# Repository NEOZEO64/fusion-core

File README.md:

# FUSION CORE (synthesizer)

## Aims

- No aim lol
- Get to know delicious circuits (experimenting a lot)
- Use them in crude ways to generate sounds
- Learn how to design circuits & professionally manufacture them with KiCad
- Learn whats possible with analog circuits and what's not
- Have a lot of fun without the need of programming

- Get an overview of electronic parts out there
- Manage a big project
- Make ambient dub techno at the end lol

## Resources
- Books
    - Make: Analog Synthesizers (from Music from outer space)
    - The Art of Electronics
    - Make: Electronics & Make: More Electronics
    - Encyclopedia of Electronic Components (Vol. 1, Vol. 2, Vol. 3)
    - Engineers Mini-Notebooks
- Internet
    - https://www.lookmumnocomputer.com/
    - https://www.eddybergman.com/
    - https://www.birthofasynth.com/Thomas_Henry/TH_main.html
    - https://musicfromouterspace.com/
    - https://www.schmitzbits.de/index.html
    - https://www.ericasynths.lv/
    - and a lot more!
- University for background theory
    - Electronics I & II
    - Signals & Systems, Control Systems
    - Communications Engineering
    - Computer Engineering

## Gallery

DIY dual 12V power supply + 5V (combined switched mode & linear regulated)

My first module! Still very early, but reliable 1V/oct frequency control and all outputs (Triangle, Saw, Rectangle) have the same voltage levels

Obviously go to Look Mum no Computer concert!

Test circuits with chaotic wiring

Borrow devices from student research center

## Module Specifications
- ±12V, 5V Power Supply
- 16cm high, n * 2cm wide (Eurorack is too small, Cosmo too large)

- PCB-Color: Green
- Different front-plate materials (wooden, metal, PVC)

# Level 1: Basic Synth

## Chapter 1: Case
- It should be a wooden box sprayed black with fancy neon art or something

## Chapter 2: PSU
- found a better one than my own diy thing (RT65-B)

## Chapter 3: 3x VCO 
- still experimenting and learning how to design modules with input / output protection
- but first VCO tests work based on AS3340/CEM3340

Knobs:
- Big Frequency Knob
- Fine Frequency Knob
- PWM Knob

Inputs:
- PWM
- 1V/Oct
- Hard Sync
- Soft Sync

Outputs:
- Triangle
- Sawtooth
- Rectangle

## Chapter 4: 2x VCF
- First design workes based on LM13700 Operational Transconductance Amplifier, but I want to make sure it workes in every situation and the output is in voltage bounds

Knobs:
- Cutoff
- Resonance
- Drive

Inputs:
- Cutoff
- Resonance
- Drive

Output:
- Low Pass
- Band pass
- High Pass

## Chapter 5: 4x VCA

VU Meter?

Knobs:
- Volume

Inputs:
- Audio in
- CV in

Outputs:
- Audio out

## Chapter 6: 2x 4-channel Mixer
Knobs:
- Channel 1 Volume
- Channel 2 Volume
- Channel 3 Volume
- Channel 4 Volume

Inputs:
- Audio Channel 1
- Audio Channel 2
- Audio Channel 3
- Audio Channel 4

Output
- Audio Sum

## Chapter 7: Teensy 4.1 as digital signal processor for reverb / echo / distortion effects

Knobs:
- Mode
- Mod 1 (Reverb Room Size    / Echo Clock Speed)
- Mod 2 (Reverb Decay Length / Echo Feedback)

Input:
- Left Audio In
- Optional Right Audio In
- Mod 1 (Reverb Room Size    / Echo Clock Speed)

Output:
- Left Audio Out
- Right Audio Out

## Chapter 8: Audio Out (Headphones, Line Out)
- Input buffering Input / Output durch OpAmp?

- Dual Mono to Stereo
- Headphone Out
- Volume Knob
- Vu Meter

# Level 3: LMNC AAAPPPCCC Module

# Level 4: Triangle to Sine Wave Conversion

# Level 5: Beat Extension

## Chapter 1: Splitter

## Chapter 2: Clock

## Chapter 3: Clock Divider

## Chapter 4: Counter

## Chapter 5: ADSR

## Chapter 6: Manual Trigger / Gate

## Chapter 7: Sample & Hold

## Chapter 8: LFO

## Chapter 9: Constant voltage source

## Chapter 10: Signal voltage offset

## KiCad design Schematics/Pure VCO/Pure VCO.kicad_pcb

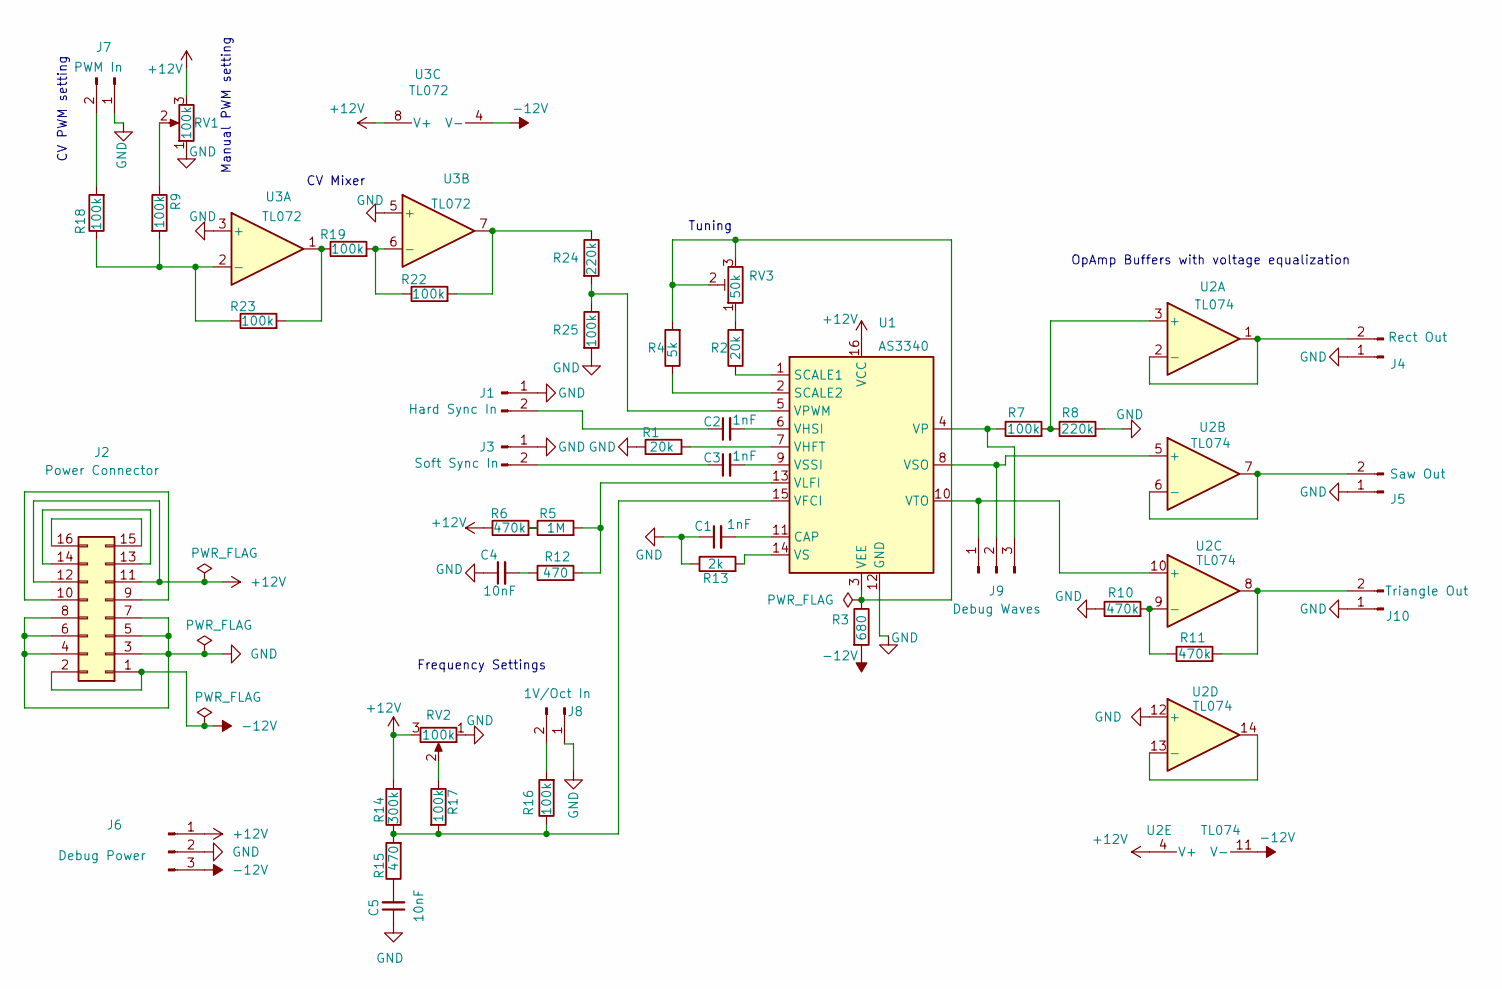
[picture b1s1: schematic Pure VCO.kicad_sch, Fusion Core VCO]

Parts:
C1: 1nF; C_Disc_D14.5mm_W5.0mm_P10.00mm
C2, C3: 1nF; C_Disc_D4.3mm_W1.9mm_P5.00mm
C4, C5: 10nF; C_Disc_D4.3mm_W1.9mm_P5.00mm
J1: Hard Sync In; PinHeader_1x02_P2.54mm_Vertical
J2: Power Connector; IDC-Header_2x08_P2.54mm_Vertical
J3: Soft Sync In; PinHeader_1x02_P2.54mm_Vertical
J4: Rect Out; PinHeader_1x02_P2.54mm_Vertical
J5: Saw Out; PinHeader_1x02_P2.54mm_Vertical
J6: Debug Power; PinHeader_1x03_P2.54mm_Vertical
J7: PWM In; PinHeader_1x02_P2.54mm_Vertical
J8: 1V/Oct In; PinHeader_1x02_P2.54mm_Vertical
J9: Debug Waves; PinHeader_1x03_P2.54mm_Vertical
J10: Triangle Out; PinHeader_1x02_P2.54mm_Vertical
R1, R2: 20k; R_Axial_DIN0207_L6.3mm_D2.5mm_P7.62mm_Horizontal
R3: 680; R_Axial_DIN0207_L6.3mm_D2.5mm_P7.62mm_Horizontal
R4: 5k; R_Axial_DIN0207_L6.3mm_D2.5mm_P7.62mm_Horizontal
R5: 1M; R_Axial_DIN0207_L6.3mm_D2.5mm_P7.62mm_Horizontal
R6, R10, R11: 470k; R_Axial_DIN0207_L6.3mm_D2.5mm_P7.62mm_Horizontal
R7, R9, R16, R17, R18, R19, R22, R23, R25: 100k; R_Axial_DIN0207_L6.3mm_D2.5mm_P7.62mm_Horizontal
R8, R24: 220k; R_Axial_DIN0207_L6.3mm_D2.5mm_P7.62mm_Horizontal
R12, R15: 470; R_Axial_DIN0207_L6.3mm_D2.5mm_P7.62mm_Horizontal
R13: 2k; R_Axial_DIN0207_L6.3mm_D2.5mm_P7.62mm_Horizontal
R14: 300k; R_Axial_DIN0207_L6.3mm_D2.5mm_P7.62mm_Horizontal
RV1, RV2: 100k; Potentiometer_Bourns_3386C_Horizontal
RV3: 50k; Potentiometer_Bourns_3266Y_Vertical
U1: AS3340; DIP-16_W7.62mm_Socket
U2: TL074; DIP-14_W7.62mm_Socket
U3: TL072; DIP-8_W7.62mm_Socket

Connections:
+12V: J2.11, J2.12, J6.1, R6.1, R14.2, RV1.3, RV2.3, U1.16 (VCC), U2.4 (V+), U3.8 (V+)
-12V: J2.1, J2.2, J6.3, R3.2, U2.11 (V-), U3.4 (V-)
GND: C1.1, C4.1, C5.1, J1.1, J2.3, J2.4, J2.5, J2.6, J2.7, J2.8, J3.1, J4.1, J5.1, J6.2, J7.1, J8.1, J10.1, R1.1, R8.2, R10.1, R13.1, R25.2, RV1.1, RV2.1, U1.12 (GND), U2.12 (+), U3.3 (+), U3.5 (+)
unnamed: C4.2, R12.1
unnamed: C5.2, R15.1
unnamed: C2.1, J1.2
unnamed: J2.9, J2.10
unnamed: J2.13, J2.14
unnamed: J2.15, J2.16
unnamed: C3.1, J3.2
unnamed: J4.2, U2.1, U2.2 (-)
unnamed: J5.2, U2.6 (-), U2.7
unnamed: J7.2, R18.2
unnamed: J8.2, R16.2
unnamed: J9.1, U1.10 (VTO), U2.10 (+)
unnamed: J9.2, U1.8 (VSO), U2.5 (+)
unnamed: J9.3, R7.1, U1.4 (VP)
unnamed: J10.2, R11.2, U2.8
unnamed: R2.2, RV3.1
unnamed: R5.1, R6.2
unnamed: R9.1, RV1.2
unnamed: R17.1, RV2.2
unnamed: R19.1, R23.2, U3.1
unnamed: R22.2, R24.1, U3.7
unnamed: C1.2, U1.11 (CAP)
unnamed: R2.1, U1.1 (SCALE1)
unnamed: R4.1, U1.2 (SCALE2)
unnamed: R3.1, R4.2, RV3.2, RV3.3, U1.3 (VEE)
unnamed: R14.1, R15.2, R16.1, R17.2, U1.15 (VFCI)
unnamed: R1.2, U1.7 (VHFT)
unnamed: C2.2, U1.6 (VHSI)
unnamed: R5.2, R12.2, U1.13 (VLFI)
unnamed: R24.2, R25.1, U1.5 (VPWM)
unnamed: R13.2, U1.14 (VS)
unnamed: C3.2, U1.9 (VSSI)
unnamed: R7.2, R8.1, U2.3 (+)
unnamed: R10.2, R11.1, U2.9 (-)
unnamed: U2.13 (-), U2.14
unnamed: R9.2, R18.1, R23.1, U3.2 (-)
unnamed: R19.2, R22.1, U3.6 (-)

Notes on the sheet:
Tuning
OpAmp Buffers with voltage equalization
CV PWM setting
Manual PWM setting
Frequency Settings
CV Mixer

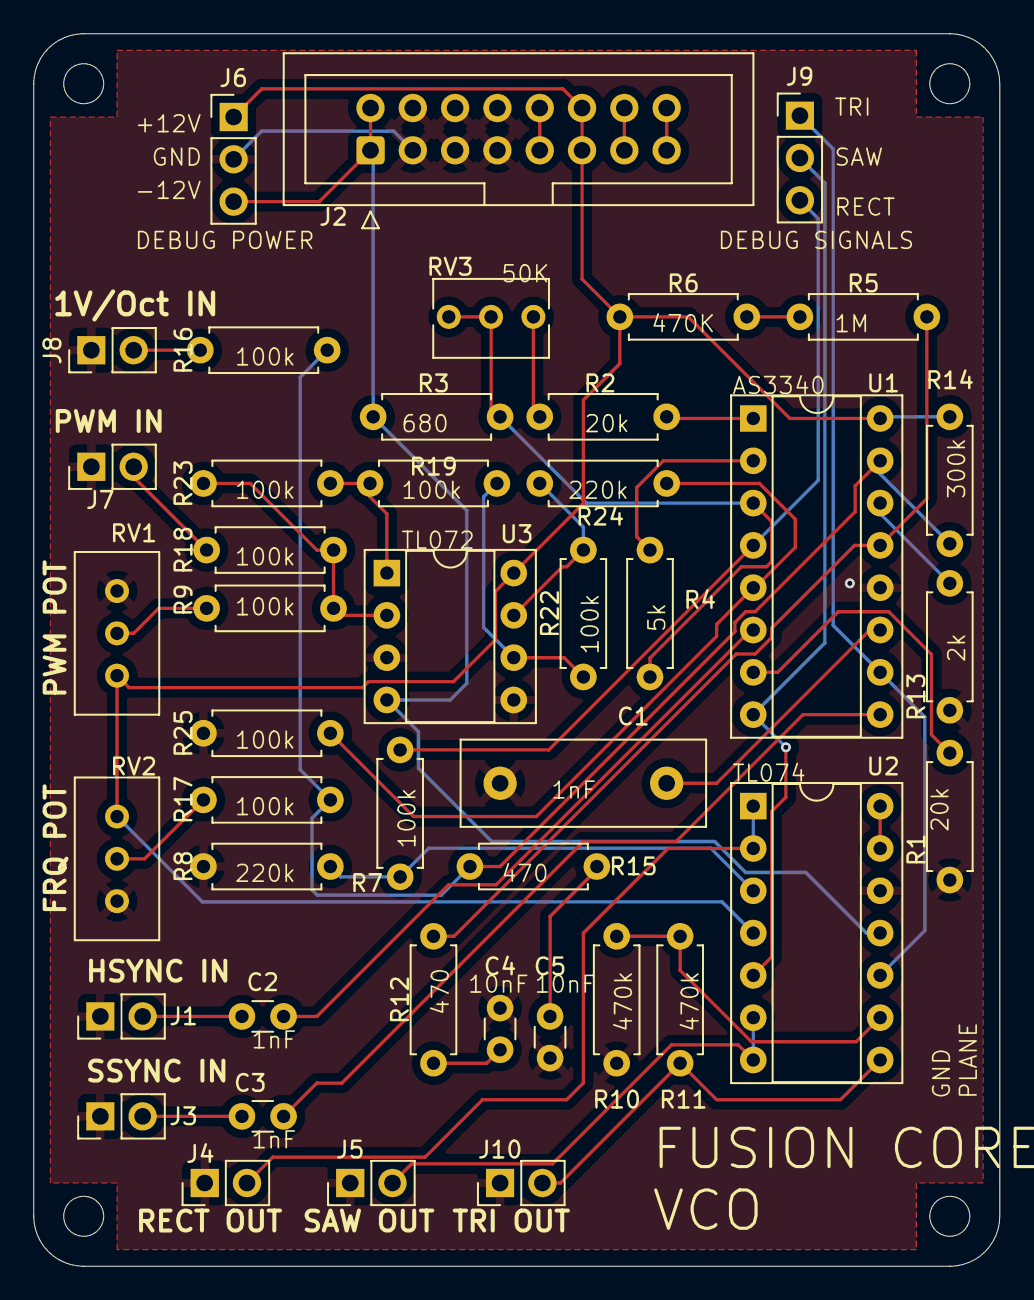
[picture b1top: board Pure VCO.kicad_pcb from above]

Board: 2 copper layers, 58.0 x 74.0 mm, 44 parts (0 on the bottom side), 40 nets.

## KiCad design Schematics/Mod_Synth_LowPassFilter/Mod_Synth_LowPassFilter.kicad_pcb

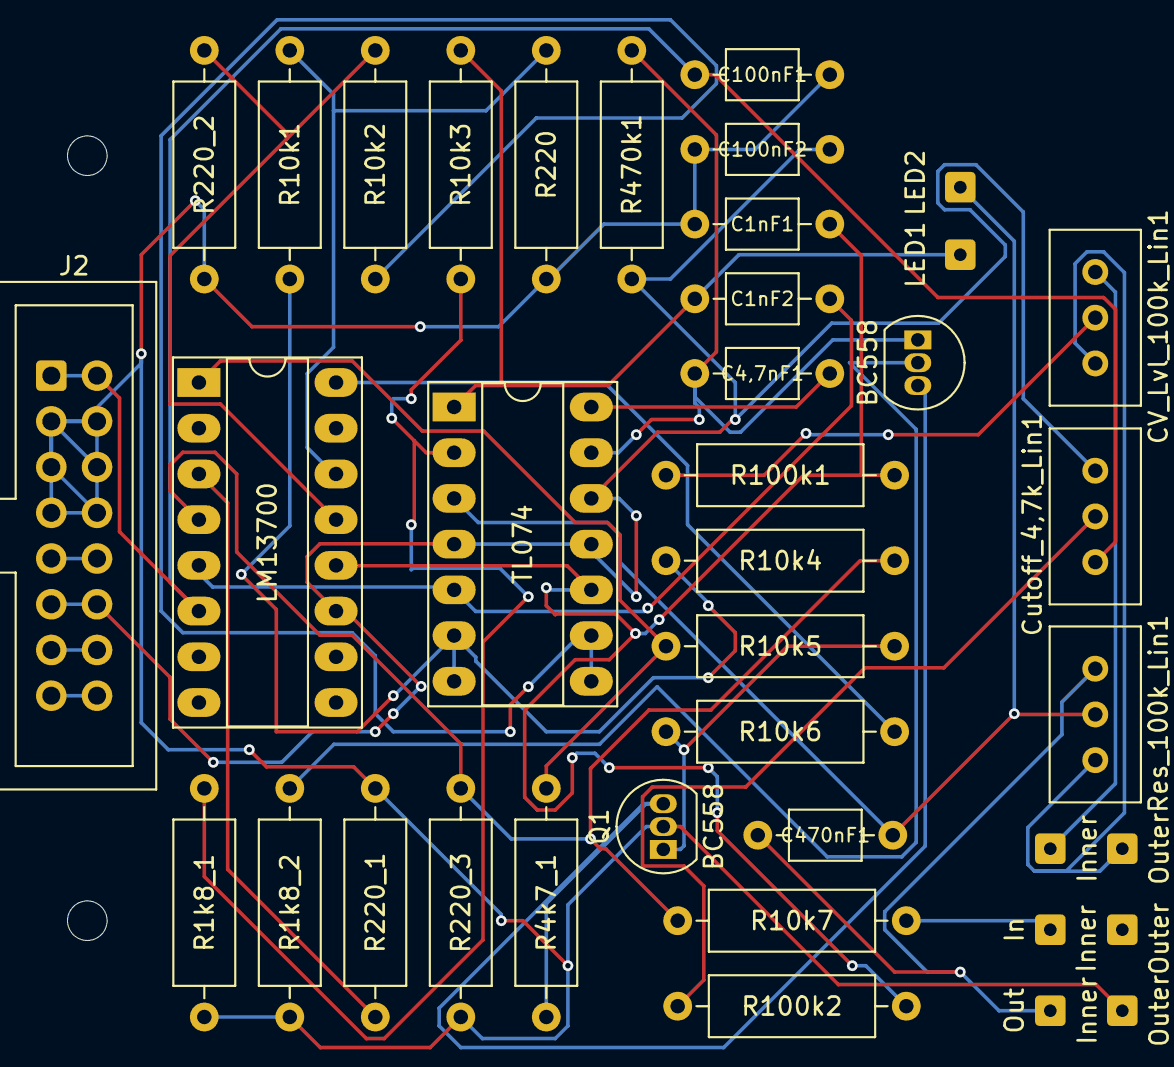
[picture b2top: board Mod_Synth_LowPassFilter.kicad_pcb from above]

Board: 2 copper layers, 39 parts (0 on the bottom side), 30 nets.

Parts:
C1nF1, C1nF2, C4,7nF1, C100nF1, C100nF2, C470nF1: C; C_Axial_L3.8mm_D2.6mm_P7.50mm_Horizontal
CV_In: Inner; SolderWire-0.15sqmm_1x01_D0.5mm_OD1.5mm
CV_InputJack2: Outer; SolderWire-0.15sqmm_1x01_D0.5mm_OD1.5mm
CV_Lvl_100k_Lin1: R_Potentiometer; Potentiometer_Bourns_3386C_Horizontal
Cutoff_4,7k_Lin1: R_Potentiometer; Potentiometer_Bourns_3386C_Horizontal
In: Inner; SolderWire-0.15sqmm_1x01_D0.5mm_OD1.5mm
InputJack2: Outer; SolderWire-0.15sqmm_1x01_D0.5mm_OD1.5mm
J2: Conn_02x08_Odd_Even; IDC-Header_2x08_P2.54mm_Vertical
LEDOutput1: LED1; SolderWire-0.15sqmm_1x01_D0.5mm_OD1.5mm
LEDOutput2: LED2; SolderWire-0.15sqmm_1x01_D0.5mm_OD1.5mm
Out: Inner; SolderWire-0.15sqmm_1x01_D0.5mm_OD1.5mm
OutputJack2: Outer; SolderWire-0.15sqmm_1x01_D0.5mm_OD1.5mm
Q1, Q2: BC558; TO-92_Inline
R1k8_1, R1k8_2, R4k7_1, R10k1, R10k2, R10k3, R10k4, R10k5, R10k6, R10k7, R100k1, R100k2, R220, R220_1, R220_2, R220_3, R470k1: R; R_Axial_DIN0309_L9.0mm_D3.2mm_P12.70mm_Horizontal
Res_100k_Lin1: R_Potentiometer; Potentiometer_Bourns_3386C_Horizontal
U1: LM13700; DIP-16_W7.62mm_Socket_LongPads
U2: TL074; DIP-14_W7.62mm_Socket_LongPads

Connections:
unnamed: C4,7nF1.2, U2.14
unnamed: CV_In.1, CV_Lvl_100k_Lin1.1
unnamed: CV_InputJack2.1, CV_Lvl_100k_Lin1.3, Res_100k_Lin1.3
unnamed: CV_Lvl_100k_Lin1.2, R100k1.1
unnamed: Cutoff_4,7k_Lin1.2, R100k2.2
unnamed: In.1, R10k7.1
unnamed: C100nF1.1, Cutoff_4,7k_Lin1.3, J2.1, J2.2, U1.6 (V-)
unnamed: C1nF1.1, C100nF1.2, C100nF2.1, J2.3, J2.4, J2.5, J2.6, J2.7, J2.8, OutputJack2.1, Q1.2 (B), R1k8_1.1, R1k8_2.1, R220.1, R220_1.2, R220_2.1, R220_3.1
unnamed: J2.9, J2.10
unnamed: C100nF2.2, Cutoff_4,7k_Lin1.1, J2.11, J2.12, R470k1.1, U1.11 (V+), U2.4 (V+), U2.11 (V-), U2.12 (+)
unnamed: J2.13, J2.14
unnamed: J2.15, J2.16
unnamed: C1nF2.1, LEDOutput1.1, R10k3.2, U2.1
unnamed: C470nF1.2, LEDOutput2.1, Res_100k_Lin1.2, U2.3 (+)
unnamed: C470nF1.1, Out.1, Res_100k_Lin1.1
unnamed: Q1.1 (C), R10k5.2, R10k6.1
unnamed: Q1.3 (E), Q2.3 (E), R4k7_1.1
unnamed: Q2.2 (B), R1k8_2.2
unnamed: C4,7nF1.1, Q2.1 (C), R470k1.2, U2.13 (-)
unnamed: R4k7_1.2, R10k5.1, U1.1
unnamed: R10k6.2, U1.16
unnamed: R10k1.2, R220.2, U1.14 (+)
unnamed: R10k2.2, R220_2.2, U1.13 (-)
unnamed: R220_1.1, U1.3 (+)
unnamed: R10k4.2, R10k7.2, R220_3.2, U1.4 (-)
unnamed: R1k8_1.2, R10k3.1, U2.2 (-)
unnamed: C1nF2.2, U1.5, U2.5 (+)
unnamed: R10k1.1, R10k4.1, U2.6 (-), U2.7
unnamed: C1nF1.2, R100k1.2, R100k2.1, U1.12, U2.10 (+)
unnamed: R10k2.1, U2.8, U2.9 (-)

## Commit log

2024-06-17 batch-upload
2024-06-17 basic comments
2024-06-17 better layout
